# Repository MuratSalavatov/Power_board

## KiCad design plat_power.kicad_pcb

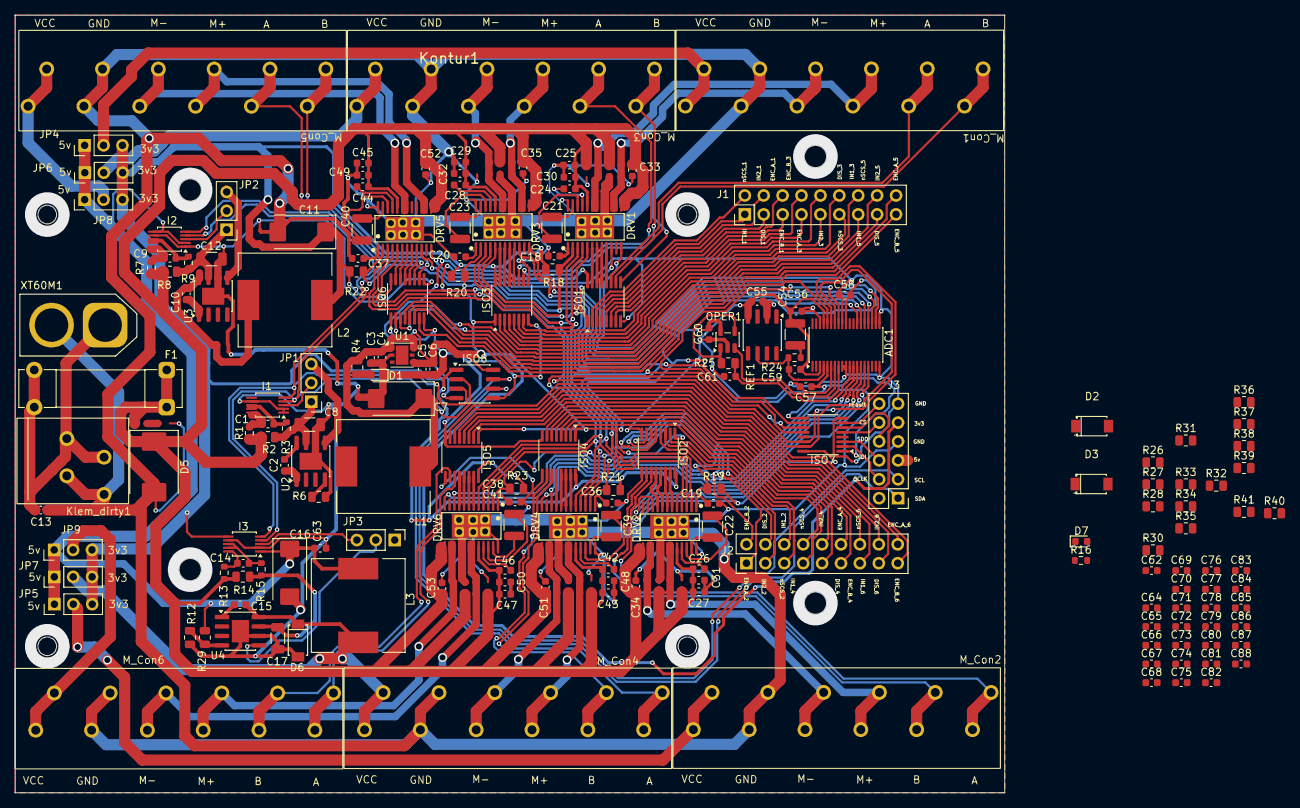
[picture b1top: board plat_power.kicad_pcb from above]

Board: 2 copper layers, 132.9 x 104.5 mm, 180 parts (0 on the bottom side), 178 nets.

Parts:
ADC1: TSSOP-38_4.4x9.7mm_P0.5mm
C1, C4, C6, C9, C13, C14, C56, C57, C58, C65, C66, C67, C68, C69, C70, C71, C72, C73, C74, C75, C76, C77, C78, C79, C80, C81, C82, C83, C84, C85: 100nF; C_0603_1608Metric
C2, C10, C15: 10nF; C_0603_1608Metric
C3, C5, C18, C19, C20, C24, C26, C28, C36, C37, C38, C42, C44, C46, C86, C87, C88: 1uF; C_0603_1608Metric
C7, C11, C16: 330uF; CP_EIA-7343-31_Kemet-D_HandSolder
C8, C12, C17: 4.7uF; C_1206_3216Metric
C21, C22, C23, C39, C40, C41, C54: 47nF; C_1210_3225Metric
C25, C27, C29, C43, C45, C47, C55, C59: 10uF; C_0603_1608Metric
C30, C31, C32, C33, C34, C35, C48, C49, C50, C51, C52, C53, C60, C62, C63, C64: 0.1uF; C_0603_1608Metric
C61: 1nF; C_0603_1608Metric
D1, D7: Green; LED_0603_1608Metric
D2, D3, D6: PMEG4050ETP,115; C552915_SOD-128_L3_7-W2_5-LS4_7-RD
D5: SS54L; D_SMC
DRV1, DRV2, DRV3, DRV4, DRV5, DRV6: DRV8873SPWPRQ1; C2150678_HTSSOP-24_L7_8-W4_4-P0_65-LS6_4-TL-EP
F1: Fuse; Fuseholder_Clip-5x20mm_Bel_FC-203-22_Lateral_P17.80x5.00mm_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
I1, I2, I3: INA226; TSSOP-10_3x3mm_P0.5mm
ISO1, ISO2, ISO3, ISO4, ISO5, ISO6, ISO7: ISO7762FDBQ; SSOP-16_3.9x4.9mm_P0.635mm
ISO8: ISO1540; SOIC-8_3.9x4.9mm_P1.27mm
J1, J2: Conn_01x18_Pin; PinHeader_2x09_P2.54mm_Vertical
J3: Conn_01x12_Pin; PinHeader_2x06_P2.54mm_Vertical
JP1, JP2, JP3, JP4, JP5, JP6, JP7, JP8, JP9: Jumper_3_Open; PinHeader_1x03_P2.54mm_Vertical
Klem_dirty1: KF202; con_klemnic
Kontur1: JetBot_AI_Kit_3x18650_Hole_Pattern
L1, L3: 15uH; L_12x12mm_H4.5mm
L2: 10uH; L_12x12mm_H4.5mm
M_Con1, M_Con2, M_Con3, M_Con4, M_Con5, M_Con6: ZX-PH2.0-6PWZ-Y; KF202-7.5-6P
OPER1: TLV9061xDBV; SOT-23-5
R1, R3, R7, R9, R13, R15, R24: 1; R_0603_1608Metric
R2, R8, R14: 10m; R_0805_2012Metric
R4: 1k; R_0805_2012Metric
R6, R12: 3.3k; R_0805_2012Metric
R16: 2.2k; R_0603_1608Metric
R18, R19, R20, R21, R22, R23, R26, R27, R29: 10k; R_0805_2012Metric
R25: 10; R_0805_2012Metric
R28: 5.9k; R_0805_2012Metric
R30, R36, R37, R38, R39, R40, R41: 240R 1%; R_0805_2012Metric
R31, R32, R33, R34, R35: 240R 0.1%; R_0805_2012Metric
REF1: REF5025AD; SOIC-8_3.9x4.9mm_P1.27mm
U1: LD39050PU33R; DFN-6-1EP_3x3mm_P0.95mm_EP1.7x2.6mm
U2, U3, U4: TPS5450; SOIC-8-1EP_3.9x4.9mm_P1.27mm_EP2.29x3mm
XT60M1: Klem2; AMASS_XT60-M_1x02_P7.20mm_Vertical

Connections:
+3,3v: C11.1, C62.2, C65.1, C66.1, C67.1, C68.1, C69.1, C70.1, C73.1, C78.1, C79.1, C80.1, C81.1, C83.1, C84.1, DRV1.11 (nSLEEP), DRV2.11 (nSLEEP), DRV3.11 (nSLEEP), DRV4.11 (nSLEEP), DRV5.11 (nSLEEP), DRV6.11 (nSLEEP), I1.6 (VS), I2.2 (A0), I2.6 (VS), I3.1 (A1), I3.6 (VS), ISO1.16 (Vcc2), ISO2.16 (Vcc2), ISO3.16 (Vcc2), ISO4.16 (Vcc2), ISO5.16 (Vcc2), ISO6.16 (Vcc2), ISO7.16 (Vcc2), ISO8.1 (VCC1), JP4.3 (B), JP5.3 (B), JP6.3 (B), JP7.3 (B), JP8.3 (B), JP9.3 (B), L2.2, R18.1, R19.1, R20.1, R21.1, R22.1, R23.1, R27.1
+3,3v*: ADC1.5 (+VA), ADC1.29 (+VA), ADC1.36 (+VBD), C5.1, C6.1, C55.1, C56.1, C57.1, C58.1, C60.2, C71.1, C72.1, C74.1, C75.1, C76.1, C77.1, C82.1, C85.1, C86.1, C87.1, C88.1, ISO1.1 (Vcc1), ISO2.1 (Vcc1), ISO3.1 (Vcc1), ISO4.1 (Vcc1), ISO5.1 (Vcc1), ISO6.1 (Vcc1), ISO7.1 (Vcc1), ISO8.8 (VCC2), J3.9, OPER1.5 (V+), REF1.2 (Vin), U1.4 (VOUT)
+5v: C16.1, C63.2, J3.5, JP4.1 (A), JP5.1 (A), JP6.1 (A), JP7.1 (A), JP8.1 (A), JP9.1 (A), L3.2, R29.1
+5v*: C3.1, C4.1, C7.1, C64.2, L1.2, R4.1, R26.1, U1.1 (EN), U1.6 (VIN)
+14.4v: C24.2, C25.1, C26.2, C27.1, C28.2, C29.1, C30.2, C31.2, C32.2, C33.2, C34.2, C35.2, C42.2, C43.1, C44.2, C45.1, C46.2, C47.1, C48.2, C49.2, C50.2, C51.2, C52.2, C53.2, D5.1 (K), DRV1.13 (VM), DRV1.20 (VM), DRV2.13 (VM), DRV2.20 (VM), DRV3.13 (VM), DRV3.20 (VM), DRV4.13 (VM), DRV4.20 (VM), DRV5.13 (VM), DRV5.20 (VM), DRV6.13 (VM), DRV6.20 (VM), F1.1, R1.2, R2.1, R7.2, R8.1, R13.2, R14.1, R16.2
CONN_1_M1: DRV1.18 (OUT1), DRV1.19 (OUT1), M_Con1.4
CONN_1_M2: DRV2.18 (OUT1), DRV2.19 (OUT1), M_Con2.3
CONN_1_M3: DRV3.18 (OUT1), DRV3.19 (OUT1), M_Con3.3
CONN_1_M4: DRV4.18 (OUT1), DRV4.19 (OUT1), M_Con4.3
CONN_1_M5: DRV5.18 (OUT1), DRV5.19 (OUT1), M_Con5.3
CONN_1_M6: DRV6.18 (OUT1), DRV6.19 (OUT1), M_Con6.4
CONN_2_M1: DRV1.14 (OUT2), DRV1.15 (OUT2), M_Con1.3
CONN_2_M2: DRV2.14 (OUT2), DRV2.15 (OUT2), M_Con2.4
CONN_2_M3: DRV3.14 (OUT2), DRV3.15 (OUT2), M_Con3.4
CONN_2_M4: DRV4.14 (OUT2), DRV4.15 (OUT2), M_Con4.4
CONN_2_M5: DRV5.14 (OUT2), DRV5.15 (OUT2), M_Con5.4
CONN_2_M6: DRV6.14 (OUT2), DRV6.15 (OUT2), M_Con6.3
CS_ISO: ADC1.31 (CS#), ISO7.12 (OUTD)
DISABLE_ISO_1: DRV1.9 (DISABLE), ISO1.12 (OUTD)
DISABLE_ISO_2: DRV2.9 (DISABLE), ISO2.12 (OUTD)
DISABLE_ISO_3: DRV3.9 (DISABLE), ISO3.12 (OUTD)
DISABLE_ISO_4: DRV4.9 (DISABLE), ISO4.12 (OUTD)
DISABLE_ISO_5: DRV5.9 (DISABLE), ISO6.12 (OUTD)
DISABLE_ISO_6: DRV6.9 (DISABLE), ISO5.12 (OUTD)
DISABLE_mk_1: ISO1.5 (IND), J1.3
DISABLE_mk_2: ISO2.5 (IND), J2.4
DISABLE_mk_3: ISO3.5 (IND), J1.10
DISABLE_mk_4: ISO4.5 (IND), J2.9
DISABLE_mk_5: ISO6.5 (IND), J1.15
DISABLE_mk_6: ISO5.5 (IND), J2.15
ENA_U2: JP1.2 (C), U2.5 (ENA)
ENA_U4: JP2.2 (C), U3.5 (ENA)
ENA_U5: JP3.2 (C), U4.5 (ENA)
ENC_A_M1: ISO1.11 (INE), M_Con1.5
ENC_A_M1_mk: ISO1.6 (OUTE), J1.6
ENC_A_M2: ISO2.11 (INE), M_Con2.1
ENC_A_M2_mk: ISO2.6 (OUTE), J2.1
ENC_A_M3: ISO3.11 (INE), M_Con3.5
ENC_A_M3_mk: ISO3.6 (OUTE), J1.7
ENC_A_M4: ISO4.11 (INE), M_Con4.1
ENC_A_M4_mk: ISO4.6 (OUTE), J2.12
ENC_A_M5: ISO6.11 (INE), M_Con5.5
ENC_A_M5_mk: ISO6.6 (OUTE), J1.18
ENC_A_M6: ISO5.11 (INE), M_Con6.1
ENC_A_M6_mk: ISO5.6 (OUTE), J2.18
ENC_B_M1: ISO1.10 (INF), M_Con1.6
ENC_B_M1_mk: ISO1.7 (OUTF), J1.5
ENC_B_M2: ISO2.10 (INF), M_Con2.2
ENC_B_M2_mk: ISO2.7 (OUTF), J2.2
ENC_B_M3: ISO3.10 (INF), M_Con3.6
ENC_B_M3_mk: ISO3.7 (OUTF), J1.8
ENC_B_M4: ISO4.10 (INF), M_Con4.2
ENC_B_M4_mk: ISO4.7 (OUTF), J2.11
ENC_B_M5: ISO6.10 (INF), M_Con5.6
ENC_B_M5_mk: ISO6.7 (OUTF), J1.17
ENC_B_M6: ISO5.10 (INF), M_Con6.2
ENC_B_M6_mk: ISO5.7 (OUTF), J2.17
EN/IN1_ISO_1: DRV1.7 (EN/IN1), ISO1.14 (OUTB)
EN/IN1_ISO_2: DRV2.7 (EN/IN1), ISO2.14 (OUTB)
EN/IN1_ISO_3: DRV3.7 (EN/IN1), ISO3.14 (OUTB)
EN/IN1_ISO_4: DRV4.7 (EN/IN1), ISO4.14 (OUTB)
EN/IN1_ISO_5: DRV5.7 (EN/IN1), ISO6.14 (OUTB)
EN/IN1_ISO_6: DRV6.7 (EN/IN1), ISO5.14 (OUTB)
EN/IN1_mk_1: ISO1.3 (INB), J1.1
EN/IN1_mk_2: ISO2.3 (INB), J2.6
EN/IN1_mk_3: ISO3.3 (INB), J1.12
EN/IN1_mk_4: ISO4.3 (INB), J2.7
EN/IN1_mk_5: ISO6.3 (INB), J1.13
EN/IN1_mk_6: ISO5.3 (INB), J2.13
GND: ADC1.3 (REFM), ADC1.6 (AGND), ADC1.9 (AINM), ADC1.10 (AGND), ADC1.19 (AGND), ADC1.20 (AGND), ADC1.30 (AGND), ADC1.35 (BDGND), C3.2, C4.2, C5.2, C6.2, C7.2, C8.1, C11.2, C12.1, C13.2, C16.2, C17.1, C18.1, C19.1, C20.1, C25.2, C27.2, C29.2, C30.1, C31.1, C32.1, C33.1, C34.1, C35.1, C36.1, C37.1, C38.1, C43.2, C45.2, C47.2, C48.1, C49.1, C50.1, C51.1, C52.1, C53.1, C54.2, C55.2, C56.2, C57.2, C58.2, C59.2, C60.1, C61.1, C62.1, C63.1, C64.1, C65.2, C66.2, C67.2, C68.2, C69.2, C70.2, C71.2, C72.2, C73.2, C74.2, C75.2, C76.2, C77.2, C78.2, C79.2, C80.2, C81.2, C82.2, C83.2, C84.2, C85.2, C86.2, C87.2, C88.2, D1.1 (K), D2.2 (A), D3.2 (A), D5.2 (A), D6.2 (A), D7.1 (K), DRV1.16 (SRC), DRV1.17 (SRC), DRV1.24 (GND), DRV1.25 (EP), DRV2.16 (SRC), DRV2.17 (SRC), DRV2.24 (GND), DRV2.25 (EP), DRV3.16 (SRC), DRV3.17 (SRC), DRV3.24 (GND), DRV3.25 (EP), DRV4.16 (SRC), DRV4.17 (SRC), DRV4.24 (GND), DRV4.25 (EP), DRV5.16 (SRC), DRV5.17 (SRC), DRV5.24 (GND), DRV5.25 (EP), DRV6.16 (SRC), DRV6.17 (SRC), DRV6.24 (GND), DRV6.25 (EP), I1.1 (A1), I1.2 (A0), I1.7 (GND), I2.1 (A1), I2.7 (GND), I3.2 (A0), I3.7 (GND), ISO1.8 (GND1), ISO1.9 (GND2), ISO2.8 (GND1), ISO2.9 (GND2), ISO3.8 (GND1), ISO3.9 (GND2), ISO4.8 (GND1), ISO4.9 (GND2), ISO5.8 (GND1), ISO5.9 (GND2), ISO6.8 (GND1), ISO6.9 (GND2), ISO7.8 (GND1), ISO7.9 (GND2), ISO8.4 (GND1), ISO8.5 (GND2), J3.7, J3.11, Klem_dirty1.2 (GND), M_Con1.2, M_Con2.5, M_Con3.2, M_Con4.5, M_Con5.2, M_Con6.5, OPER1.2 (V-), R6.2, R12.2, R28.2, R30.2, R31.2, R32.2, R33.2, R34.2, R35.2, R36.2, R37.2, R38.2, R40.2, R41.2, REF1.4 (GND), U1.2 (GND), U1.7 (EXP), U2.6 (GND), U2.9 (GND), U3.6 (GND), U3.9 (GND), U4.6 (GND), U4.9 (GND), XT60M1.2
IPROPI1_1: ADC1.22 (CH6), DRV1.10 (IPROPI1), R30.1
IPROPI1_2: ADC1.15 (CH11), DRV2.10 (IPROPI1), R31.1
IPROPI1_3: ADC1.24 (CH4), DRV3.10 (IPROPI1), R32.1
IPROPI1_4: ADC1.13 (CH13), DRV4.10 (IPROPI1), R35.1
IPROPI1_5: ADC1.26 (CH2), DRV5.10 (IPROPI1), R34.1
IPROPI1_6: ADC1.11 (CH15), DRV6.10 (IPROPI1), R33.1
IPROPI2_1: ADC1.21 (CH7), DRV1.12 (IPROPI2), R36.1
IPROPI2_2: ADC1.16 (CH10), DRV2.12 (IPROPI2), R39.1
IPROPI2_3: ADC1.23 (CH5), DRV3.12 (IPROPI2), R40.1
IPROPI2_4: ADC1.14 (CH12), DRV4.12 (IPROPI2), R37.1
IPROPI2_5: ADC1.25 (CH3), DRV5.12 (IPROPI2), R38.1
IPROPI2_6: ADC1.12 (CH14), DRV6.12 (IPROPI2), R41.1
unnamed: ADC1.8 (AINP), C61.2, R25.2
unnamed: ADC1.7 (MXO), OPER1.3 (+)
unnamed: ADC1.4 (REFP), C59.1, R24.1, REF1.6 (Vout)
unnamed: C54.1, R24.2
unnamed: D1.2 (A), R4.2
unnamed: C2.2, D2.1 (C), L1.1, U2.8 (PH)
unnamed: C10.2, D3.1 (C), L2.1, U3.8 (PH)
unnamed: C15.2, D6.1 (C), L3.1, U4.8 (PH)
unnamed: D7.2 (A), R16.1
unnamed: C21.2, DRV1.22 (CPH)
unnamed: C21.1, DRV1.23 (CPL)
unnamed: C18.2, DRV1.1 (DVDD)
unnamed: C24.1, DRV1.21 (VCP)
unnamed: C22.2, DRV2.22 (CPH)
unnamed: C22.1, DRV2.23 (CPL)
unnamed: C19.2, DRV2.1 (DVDD)
unnamed: C26.1, DRV2.21 (VCP)
unnamed: C23.2, DRV3.22 (CPH)
unnamed: C23.1, DRV3.23 (CPL)
unnamed: C20.2, DRV3.1 (DVDD)
unnamed: C28.1, DRV3.21 (VCP)
unnamed: C39.2, DRV4.22 (CPH)
unnamed: C39.1, DRV4.23 (CPL)
unnamed: C36.2, DRV4.1 (DVDD)
unnamed: C42.1, DRV4.21 (VCP)
unnamed: C40.2, DRV5.22 (CPH)
unnamed: C40.1, DRV5.23 (CPL)
unnamed: C37.2, DRV5.1 (DVDD)
unnamed: C44.1, DRV5.21 (VCP)
unnamed: C41.2, DRV6.22 (CPH)
unnamed: C41.1, DRV6.23 (CPL)
unnamed: C38.2, DRV6.1 (DVDD)
unnamed: C46.1, DRV6.21 (VCP)
unnamed: I1.3 (Alert), JP1.3 (B)
unnamed: C1.1, I1.10 (IN+), R1.1
unnamed: C1.2, I1.8 (VBUS), I1.9 (IN-), R3.1
unnamed: I2.3 (Alert), JP2.3 (B)
unnamed: C9.1, I2.10 (IN+), R7.1
unnamed: C9.2, I2.8 (VBUS), I2.9 (IN-), R9.1
unnamed: I3.3 (Alert), JP3.3 (B)
unnamed: C14.1, I3.10 (IN+), R13.1
unnamed: C14.2, I3.8 (VBUS), I3.9 (IN-), R15.1
unnamed: ISO7.2 (INA), J3.4
unnamed: ISO7.3 (INB), J3.6
unnamed: ISO7.5 (IND), J3.10
unnamed: ISO7.6 (OUTE), J3.8
unnamed: ISO7.7 (OUTF), J3.12
unnamed: ISO8.6 (SCL2), J3.3
unnamed: ISO8.7 (SDA2), J3.1
unnamed: JP4.2 (C), M_Con1.1
unnamed: JP5.2 (C), M_Con2.6
unnamed: JP6.2 (C), M_Con3.1
unnamed: JP7.2 (C), M_Con4.6
unnamed: JP8.2 (C), M_Con5.1
unnamed: JP9.2 (C), M_Con6.6
unnamed: C13.1, F1.2, Klem_dirty1.1 (VIN), XT60M1.1
unnamed: OPER1.1, OPER1.4 (-), R25.1
unnamed: C2.1, U2.1 (BOOT)
unnamed: C8.2, R2.2, R3.2, U2.7 (VIN)
unnamed: R6.1, R26.2, U2.4 (VSENSE)
unnamed: C10.1, U3.1 (BOOT)
unnamed: C12.2, R8.2, R9.2, U3.7 (VIN)
unnamed: R27.2, R28.1, U3.4 (VSENSE)
unnamed: C15.1, U4.1 (BOOT)
unnamed: C17.2, R14.2, R15.2, U4.7 (VIN)
unnamed: R12.1, R29.2, U4.4 (VSENSE)
PH/IN2_ISO_1: DRV1.8 (PH/IN2), ISO1.13 (OUTC)
PH/IN2_ISO_2: DRV2.8 (PH/IN2), ISO2.13 (OUTC)
PH/IN2_ISO_3: DRV3.8 (PH/IN2), ISO3.13 (OUTC)
PH/IN2_ISO_4: DRV4.8 (PH/IN2), ISO4.13 (OUTC)
PH/IN2_ISO_5: DRV5.8 (PH/IN2), ISO6.13 (OUTC)
PH/IN2_ISO_6: DRV6.8 (PH/IN2), ISO5.13 (OUTC)
PH/IN2_mk_1: ISO1.4 (INC), J1.4
PH/IN2_mk_2: ISO2.4 (INC), J2.3
PH/IN2_mk_3: ISO3.4 (INC), J1.9
PH/IN2_mk_4: ISO4.4 (INC), J2.10
PH/IN2_mk_5: ISO6.4 (INC), J1.16
PH/IN2_mk_6: ISO5.4 (INC), J2.16
SCLK_ISO: ADC1.32 (SCLK), DRV1.5 (SCLK), DRV2.5 (SCLK), DRV3.5 (SCLK), DRV4.5 (SCLK), DRV5.5 (SCLK), DRV6.5 (SCLK), ISO7.15 (OUTA)
SCL_INA: I1.5 (SCL), I2.5 (SCL), I3.5 (SCL), ISO8.3 (SCL1)
SDA_INA: I1.4 (SDA), I2.4 (SDA), I3.4 (SDA), ISO8.2 (SDA1)
SDI_ISO: ADC1.33 (SDI), DRV1.4 (SDI), DRV2.4 (SDI), DRV3.4 (SDI), DRV4.4 (SDI), DRV5.4 (SDI), DRV6.4 (SDI), ISO7.14 (OUTB)
SDO_ISO: ADC1.34 (SDO), DRV1.3 (SDO), DRV2.3 (SDO), DRV3.3 (SDO), DRV4.3 (SDO), DRV5.3 (SDO), DRV6.3 (SDO), ISO7.11 (INE)
nFault_ISO: DRV1.2 (nFAULT), DRV2.2 (nFAULT), DRV3.2 (nFAULT), DRV4.2 (nFAULT), DRV5.2 (nFAULT), DRV6.2 (nFAULT), ISO7.10 (INF), R18.2, R19.2, R20.2, R21.2, R22.2, R23.2
nSCS_ISO_1: DRV1.6 (nSCS), ISO1.15 (OUTA)
nSCS_ISO_2: DRV2.6 (nSCS), ISO2.15 (OUTA)
nSCS_ISO_3: DRV3.6 (nSCS), ISO3.15 (OUTA)
nSCS_ISO_4: DRV4.6 (nSCS), ISO4.15 (OUTA)
nSCS_ISO_5: DRV5.6 (nSCS), ISO6.15 (OUTA)
nSCS_ISO_6: DRV6.6 (nSCS), ISO5.15 (OUTA)
nSCS_mk_1: ISO1.2 (INA), J1.2
nSCS_mk_2: ISO2.2 (INA), J2.5
nSCS_mk_3: ISO3.2 (INA), J1.11
nSCS_mk_4: ISO4.2 (INA), J2.8
nSCS_mk_5: ISO6.2 (INA), J1.14
nSCS_mk_6: ISO5.2 (INA), J2.14
